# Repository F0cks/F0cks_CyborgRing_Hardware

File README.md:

# F0cks_CyborgRing_Hardware

I have created my own hardware and software of **Zach Fredin** [zakqwy](https://github.com/zakqwy) Cyborg ring. You can use [my Cyborg ring software](https://github.com/F0cks/F0cks_CyborgRing_Hardware) for this hardware. <br />
You can find more information on my blog : [blog.f0cks.net/projects/Cyborg-ring](https://blog.f0cks.net/projects/Cyborg-ring/).

### Description

* This hardware has been created with **Eagle Version 7.7.0**.
* All GERBER files are included in **F0cks_CyborgRing_Gerber.zip**.
* You can create directly your board using my **OSHPark Project**: <br /> <a href="https://oshpark.com/shared_projects/YXsu5wAr"></img></a>
* I have added the **BOM** with component links from Digikey (and button cells from eBay).
* You will probably need to edit the board to fit the ring to your finger ( diameter is around 17mm).

## Authors

* **Geoffrey Enjolras** - [F0cks](https://github.com/F0cks)

## License

In agreement with **Zach Fredin**, this code is released under the terms of the Creative Commons Attribution-ShareAlike 4.0 license, available here: http://creativecommons.org/licenses/by-sa/4.0/.

## Acknowledgments

Completely inspired by **Zach Fredin** [zakqwy](https://github.com/zakqwy).

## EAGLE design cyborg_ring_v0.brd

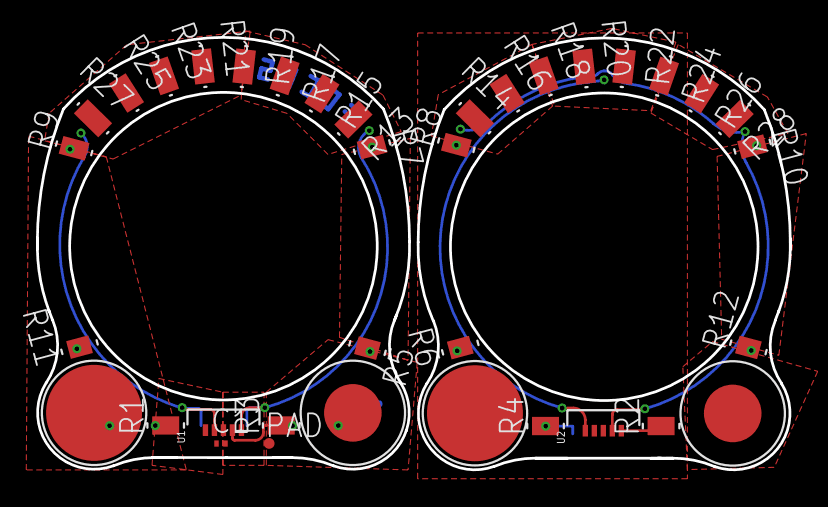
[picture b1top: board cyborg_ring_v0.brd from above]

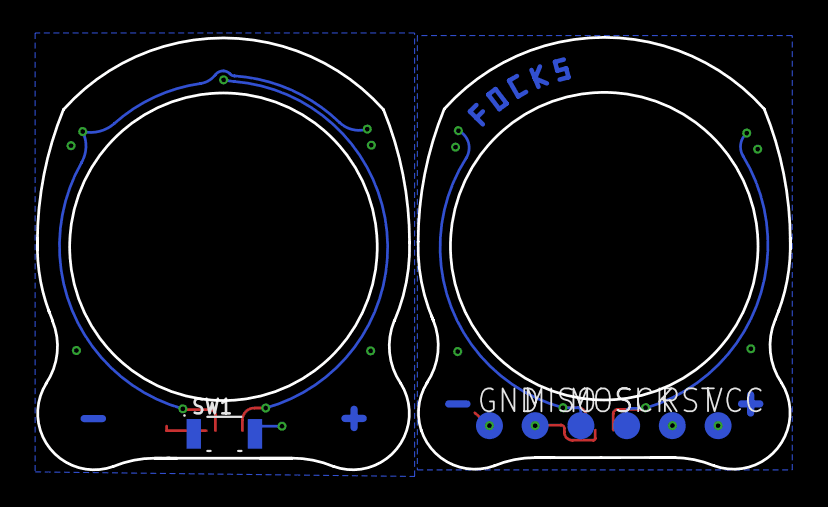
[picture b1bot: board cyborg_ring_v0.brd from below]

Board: 2 copper layers, 41.8 x 24.0 mm, 43 parts (7 on the bottom side), 13 nets.

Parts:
C1: 100n; C0201
GND: TPTP15R; TP15R
MISO: TPTP15R; TP15R
MOSI: TPTP15R; TP15R
PAD: TPTP06R; TP06R
R1, R2, R3, R4, R7, R8, R9, R10: R0805-1/2TEST; R0805-1/2
R5, R6, R11, R12: R0805-1/2TEST2; R0905-1/2BIS
R13, R14, R15, R16, R17, R18, R19, R20, R21, R22, R23, R24, R25, R26, R27, R28: R0508-1/2
RST: TPTP15R; TP15R
SCK: TPTP15R; TP15R
SW1: BTN_CK_KSS
U1: ATTINYX5V-LEFT; 1/4-QFN20
U2: ATTINYX5V-RIGHT; 1/4-QFN20
U$1, U$2: BAT+
U$3, U$4: BAT-
VCC: TPTP15R; TP15R

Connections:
GND: C1.2, GND.TP, PAD.TP, R7.1, U$4.P$1
GND1: R8.1, SW1.P$1
MISO/SW: MISO.TP, R3.1, U1.4
MOSI/L1: MOSI.TP, R13.P$1, R15.P$1, R17.P$1, R19.P$1, U1.5
R0: R14.P$1, R16.P$1, R26.P$1, R28.P$1, U2.4
R1: R18.P$1, R20.P$1, R22.P$1, R24.P$1, U2.1
RST: R1.1, RST.TP
RST1: R2.1, U2.5
SCK/L0: R21.P$1, R23.P$1, R25.P$1, R27.P$1, SCK.TP, U1.2
SWITCH1: R4.1, SW1.P$2
VCC: C1.1, R9.1, R11.1, U1.1, U$1.P$1, VCC.TP
VCC": R10.1, R12.1
VCC/2: R6.1, U$2.P$1, U$3.P$1

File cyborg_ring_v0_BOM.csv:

Qty,Value,Device,Package,Parts,Links
1,,PUSHBUTTON,BTN_CK_KSS,SW1,https://www.digikey.fr/product-detail/fr/omron-electronics-i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
1,100n,C-EUC0201,C0201,C1,https://www.digikey.fr/product-detail/fr/samsung-electro-mec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
1,ATTINYX5V-LEFT,ATTINYX5V-LEFT,1/4-QFN20,U1,https://www.digikey.fr/product-detail/fr/microchip-technolog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
0,ATTINYX5V-RIGHT,ATTINYX5V-RIGHT,1/4-QFN20,U2,/
2,BAT+,BAT+,BAT+,"U$1, U$2",https://www.ebay.fr/itm/Lot-de-piles-boutons-auditives-Rayov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
2,BAT-,BAT-,BAT-,"U$3, U$4",https://www.digikey.fr/product-detail/fr/te-connectivity-amp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
16,R0508-1/2,R0508-1/2,R0508-1/2,"R13, R14, R15, R16, R17, R18, R19, R20, R21, R22, R23, R24, R25, R26, R27, R28",https://www.digikey.fr/product-detail/fr/rohm-semiconductor/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 
12,R0805-1/2,R0805-1/2,R0805-1/2,"R1, R2, R3, R4, R5, R6, R7, R8, R9, R10, R11, R12",https://www.digikey.fr/product-detail/fr/yageo/RC0805JR-070R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
1,TPTP06R,TPTP06R,TP06R,PAD,/
6,TPTP15R,TPTP15R,TP15R,"GND, MISO, MOSI, RST, SCK, VCC",https://www.digikey.fr/product-detail/fr/mill-max-manufactur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
8,,LEDS,,,https://www.digikey.fr/product-detail/fr/kingbright/APT1608L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

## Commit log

2018-05-18 Schematic
2018-05-22 Board
2018-05-29 Clean files
2018-05-29 Adding GERBER files
2018-05-29 Adding README.md
2018-05-30 Clearer schematic
2018-05-30 BOM added
2018-05-30 README.md updated
2018-05-30 Schematic and board in .pdf added
2018-06-04 LICENSE file added
